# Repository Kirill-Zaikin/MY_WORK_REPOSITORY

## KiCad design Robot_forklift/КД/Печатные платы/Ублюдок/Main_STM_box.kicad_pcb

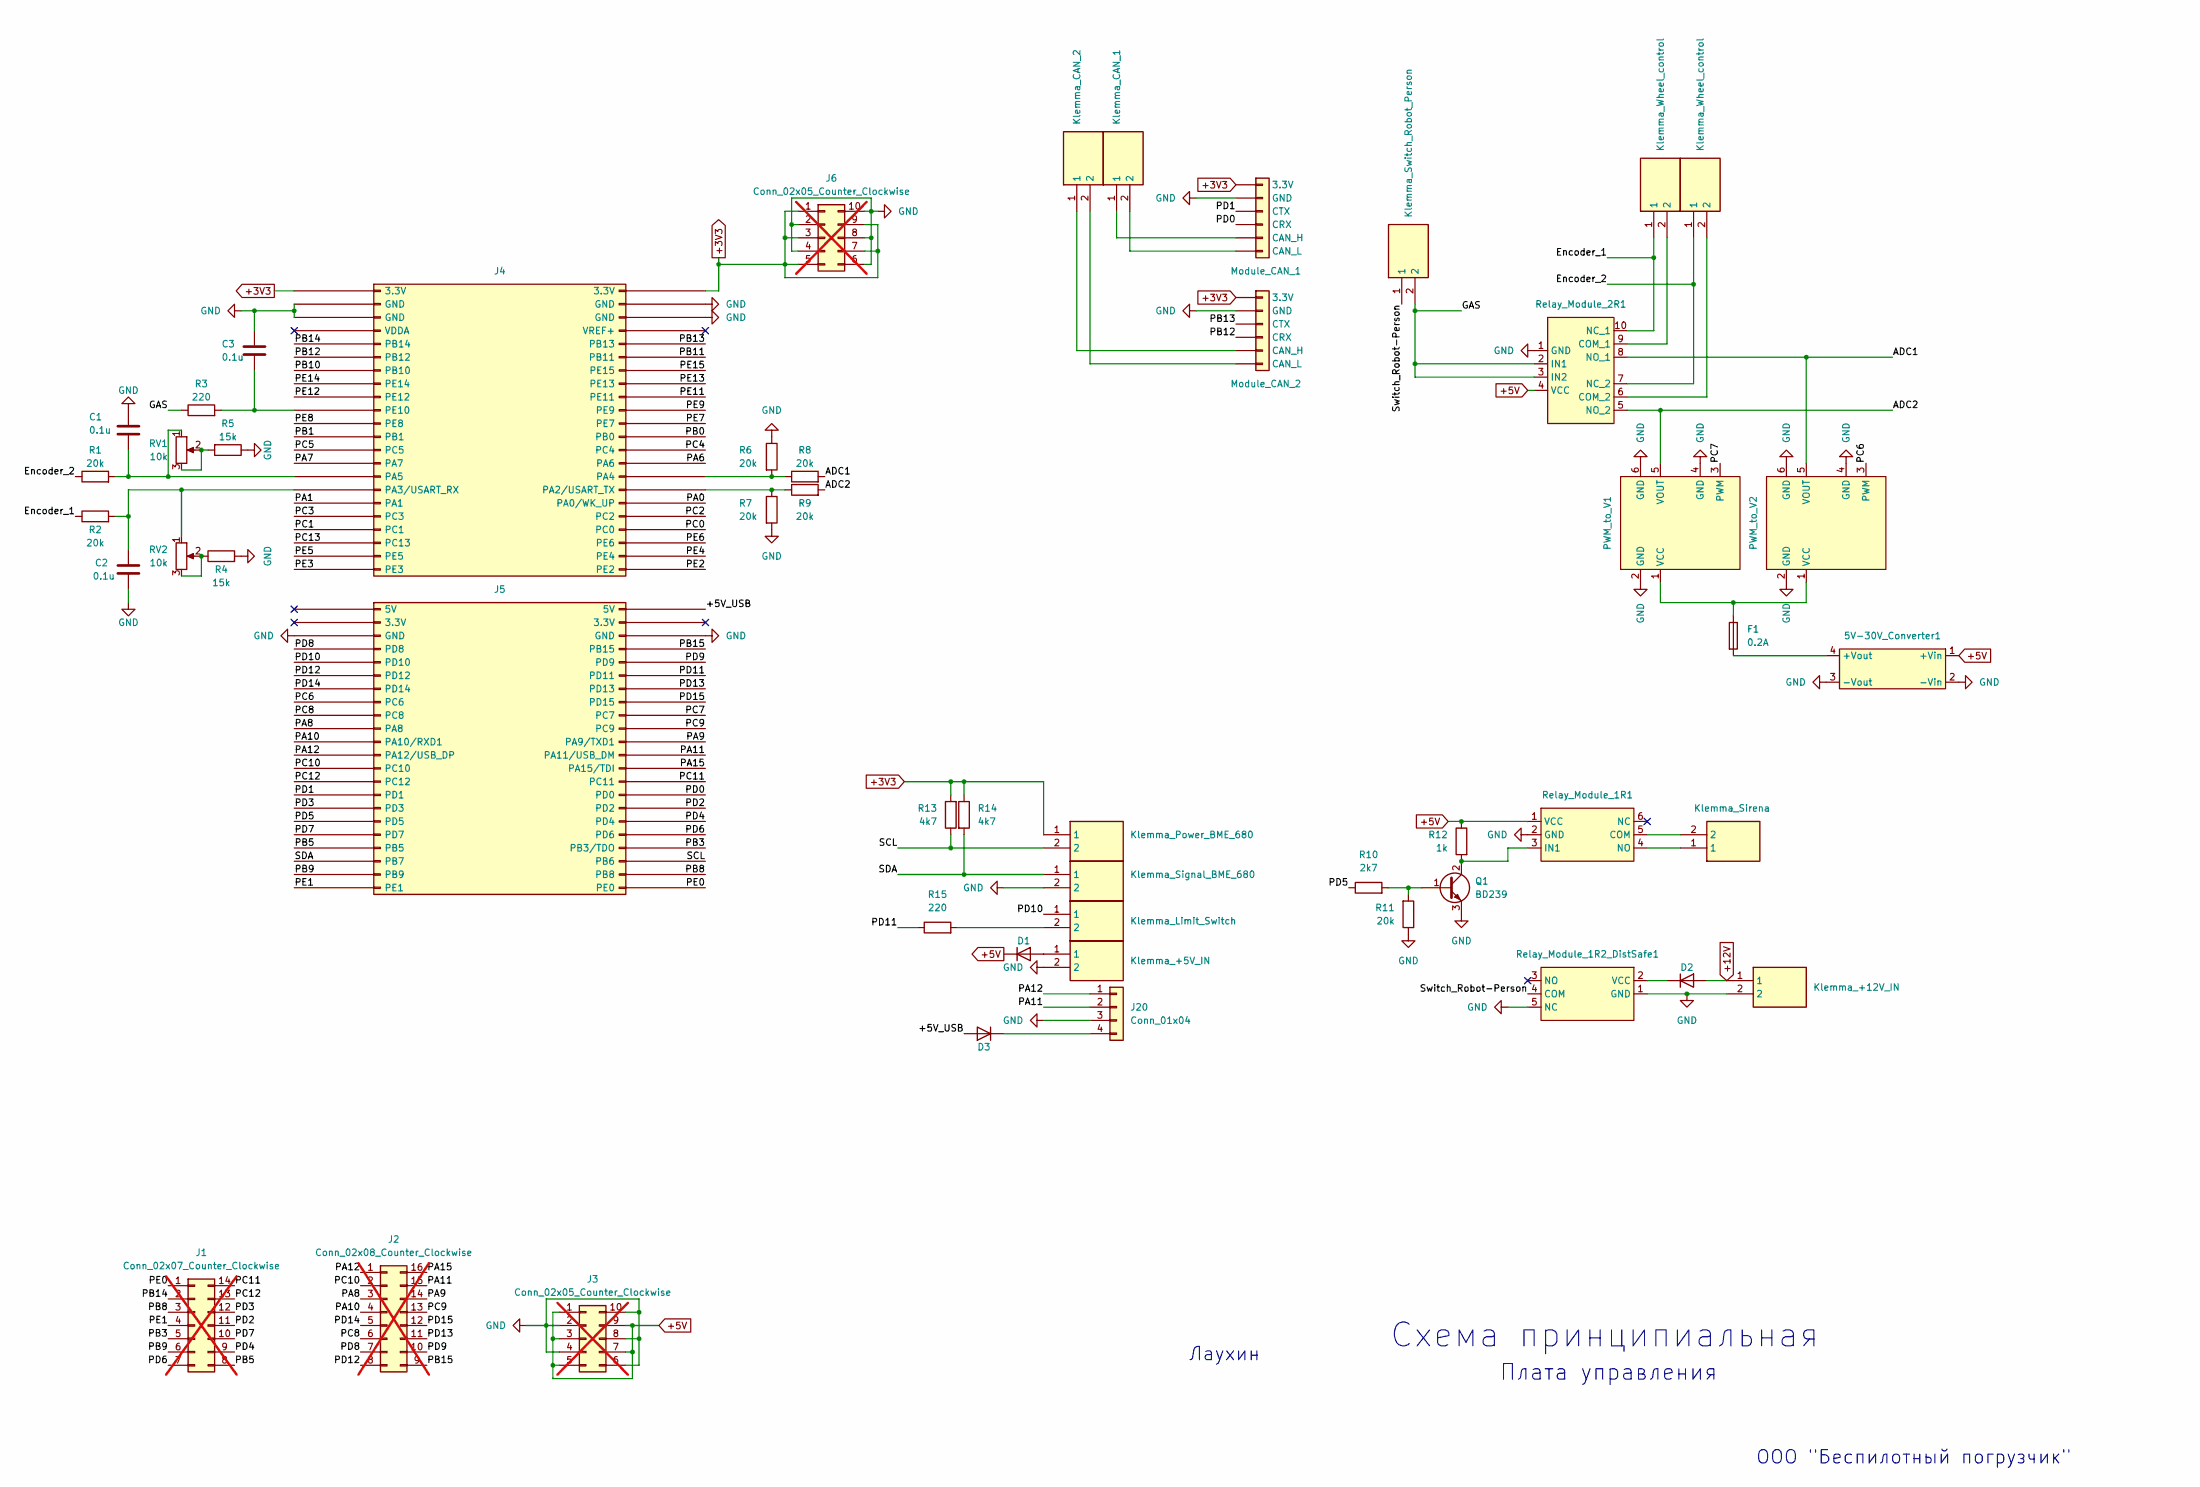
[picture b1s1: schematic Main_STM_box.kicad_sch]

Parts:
5V-30V_Converter1: 5V-30V_Converter; Manufacturer_Part_Number PBS-8 (DS-1023 -1x 8)
C1, C2, C3: 0.1u; C_Axial_L3.8mm_D2.6mm_P10.00mm_Horizontal; Manufacturer_Part_Number К10-17Б 0.1 мкФ X7R,10%, 1206, JYM1H104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
D1, D2, D3: D; D_A-405_P7.62mm_Horizontal; Manufacturer_Part_Number 1N4002
F1: 0.2A; FuseHolder_5x20mm; Manufacturer_Part_Number 2672 пред держ 5x20\закр\2P\\\
J1: Conn_02x07_Counter_Clockwise; PinHeader_2x07_P2.54mm_Vertical; not fitted
J2: Conn_02x08_Counter_Clockwise; PinHeader_2x08_P2.54mm_Vertical; not fitted
J3, J6: Conn_02x05_Counter_Clockwise; PinHeader_2x05_P2.54mm_Vertical; not fitted
J4, J5: Conn_02x22_Odd_Even; PinSocket_2x22_P2.54mm_Vertical; Manufacturer_Part_Number PBD-44 (DS1023-2x22S21)
J7: Klemma_Power_BME_680; KF3012P; Manufacturer_Part_Number KF301-2P
J8: Klemma_Signal_BME_680; KF3012P; Manufacturer_Part_Number KF301-2P
J9: Klemma_Limit_Switch; KF3012P; Manufacturer_Part_Number KF301-2P
J10: Klemma_+5V_IN; KF3012P; Manufacturer_Part_Number KF301-2P
J11: Klemma_CAN_2; KF3012P; Manufacturer_Part_Number KF301-2P
J12: Klemma_CAN_1; KF3012P; Manufacturer_Part_Number KF301-2P
J13: Module_CAN_1; WCMCU-230; Manufacturer_Part_Number PBD-12 (DS-1023 - 2x6)
J14: Module_CAN_2; WCMCU-230; Manufacturer_Part_Number PBD-12 (DS-1023 - 2x6)
J15: Klemma_Switch_Robot_Person; KF3012P; Manufacturer_Part_Number KF301-2P
J16, J18: Klemma_Wheel_control; KF3012P; Manufacturer_Part_Number KF301-2P
J17: Klemma_Sirena; KF3012P; Manufacturer_Part_Number KF301-2P
J19: Klemma_+12V_IN; KF3012P; Manufacturer_Part_Number KF301-2P
J20: Conn_01x04; JST_XH_B4B-XH-A_1x04_P2.50mm_Vertical
PWM_to_V1, PWM_to_V2: PWMtoV; Manufacturer_Part_Number PBS-3 (DS-1023 - 1x3)
Q1: BD239; Q_Transistor_footprint_NPN_PNP; Manufacturer_Part_Number BD239BTU
R1, R2, R6, R7, R8, R9, R11: 20k; R_Axial_DIN0207_L6.3mm_D2.5mm_P7.62mm_Horizontal; Manufacturer_Part_Number MF-25 (С2-23) 0.25 Вт, 20 кОм, 1%
R3: 220; R_Axial_DIN0207_L6.3mm_D2.5mm_P7.62mm_Horizontal; Manufacturer_Part_Number MF-25 (С2-23) 0.25 Вт, 220 Ом, 1%
R4, R5: 15k; R_Axial_DIN0207_L6.3mm_D2.5mm_P7.62mm_Horizontal; Manufacturer_Part_Number MF-25 (С2-23) 0.25 Вт, 15 кОм, 1%
R10: 2k7; R_Axial_DIN0207_L6.3mm_D2.5mm_P7.62mm_Horizontal; Manufacturer_Part_Number MF-25 (С2-23) 0.25 Вт, 2.7 кОм, 1%
R12: 1k; R_Axial_DIN0207_L6.3mm_D2.5mm_P7.62mm_Horizontal; Manufacturer_Part_Number MF-25 (С2-23) 0.25 Вт, 1 кОм, 1%
R13, R14: 4k7; R_Axial_DIN0207_L6.3mm_D2.5mm_P7.62mm_Horizontal; Manufacturer_Part_Number MF-25 (С2-23) 0.25 Вт, 4.7 кОм, 1%
R15: 220; R_Axial_DIN0207_L6.3mm_D2.5mm_P7.62mm_Horizontal
RV1, RV2: 10k; VSE_Potentiometers_W103_3296; Manufacturer_Part_Number 3296W-1-103LF (СП5-2ВБ), 10 кОм
Relay_Module_1R1: Relay_Module_1R; Manufacturer_Part_Number PBS-5 (DS-1023 - 1x5) + PBS-3 (DS-1023 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
Relay_Module_1R2_DistSafe1: Distance_Relay_Module; Manufacturer_Part_Number PBS-3 (DS-1023 - 1x3) + PBS-9 (DS1023-1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
Relay_Module_2R1: Relay_Module_2R; Manufacturer_Part_Number PBS-4 (DS-1023 - 1x4) + PBS-11 (DS1023-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

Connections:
+3V3: J4.1 (3.3V), J4.2 (3.3V), J6.1, J6.3, J6.5, J6.7, J6.9, J7.1, J13.1 (3.3V), J14.1 (3.3V), R13.2, R14.1
+5V: 5V-30V_Converter1.1 (+Vin), D1.1 (K), J3.1, J3.3, J3.5, J3.7, J3.9, R12.1, Relay_Module_1R1.1 (VCC), Relay_Module_2R1.4 (VCC)
+12V: D2.2 (A), J19.1
/+5V_USB: D3.2 (A), J5.2 (5V)
/ADC1: PWM_to_V2.5 (VOUT), R8.2, Relay_Module_2R1.8 (NO_1)
/ADC2: PWM_to_V1.5 (VOUT), R9.2, Relay_Module_2R1.5 (NO_2)
/Encoder_1: J16.1, R2.1, Relay_Module_2R1.10 (NC_1)
/Encoder_2: J18.1, R1.1, Relay_Module_2R1.7 (NC_2)
/GAS: J15.2, R3.1, Relay_Module_2R1.2 (IN1), Relay_Module_2R1.3 (IN2)
/PA0: J4.34 (PA0/WK_UP)
/PA1: J4.33 (PA1)
/PA6: J4.28 (PA6)
/PA7: J4.27 (PA7)
/PA8: J2.3, J5.19 (PA8)
/PA9: J2.14, J5.22 (PA9/TXD1)
/PA10: J2.4, J5.21 (PA10/RXD1)
/PA11: J2.15, J5.24 (PA11/USB_DM), J20.2
/PA12: J2.1, J5.23 (PA12/USB_DP), J20.1
/PA15: J2.16, J5.26 (PA15/TDI)
/PB0: J4.24 (PB0)
/PB1: J4.23 (PB1)
/PB3: J1.5, J5.38 (PB3/TDO)
/PB5: J1.8, J5.37 (PB5)
/PB8: J1.3, J5.42 (PB8)
/PB9: J1.6, J5.41 (PB9)
/PB10: J4.13 (PB10)
/PB11: J4.12 (PB11)
/PB12: J4.11 (PB12), J14.4 (CRX)
/PB13: J4.10 (PB13), J14.3 (CTX)
/PB14: J1.2, J4.9 (PB14)
/PB15: J2.9, J5.8 (PB15)
/PC0: J4.38 (PC0)
/PC1: J4.37 (PC1)
/PC2: J4.36 (PC2)
/PC3: J4.35 (PC3)
/PC4: J4.26 (PC4)
/PC5: J4.25 (PC5)
/PC6: J5.15 (PC6), PWM_to_V2.3 (PWM)
/PC7: J5.18 (PC7), PWM_to_V1.3 (PWM)
/PC8: J2.6, J5.17 (PC8)
/PC9: J2.13, J5.20 (PC9)
/PC10: J2.2, J5.25 (PC10)
/PC11: J1.14, J5.28 (PC11)
/PC12: J1.13, J5.27 (PC12)
/PC13: J4.39 (PC13)
/PD0: J5.30 (PD0), J13.4 (CRX)
/PD1: J5.29 (PD1), J13.3 (CTX)
/PD2: J1.11, J5.32 (PD2)
/PD3: J1.12, J5.31 (PD3)
/PD4: J1.9, J5.34 (PD4)
/PD5: J5.33 (PD5), R10.1
/PD6: J1.7, J5.36 (PD6)
/PD7: J1.10, J5.35 (PD7)
/PD8: J2.7, J5.7 (PD8)
/PD9: J2.10, J5.10 (PD9)
/PD10: J5.9 (PD10), J9.1
/PD11: J5.12 (PD11), R15.1
/PD12: J2.8, J5.11 (PD12)
/PD13: J2.11, J5.14 (PD13)
/PD14: J2.5, J5.13 (PD14)
/PD15: J2.12, J5.16 (PD15)
/PE0: J1.1, J5.44 (PE0)
/PE1: J1.4, J5.43 (PE1)
/PE2: J4.44 (PE2)
/PE3: J4.43 (PE3)
/PE4: J4.42 (PE4)
/PE5: J4.41 (PE5)
/PE6: J4.40 (PE6)
/PE7: J4.22 (PE7)
/PE8: J4.21 (PE8)
/PE9: J4.20 (PE9)
/PE11: J4.18 (PE11)
/PE12: J4.17 (PE12)
/PE13: J4.16 (PE13)
/PE14: J4.15 (PE14)
/PE15: J4.14 (PE15)
/SCL: J5.40 (PB6), J7.2, R13.1
/SDA: J5.39 (PB7), J8.1, R14.2
/Switch_Robot-Person: J15.1, Relay_Module_1R2_DistSafe1.4 (COM)
GND: 5V-30V_Converter1.2 (-Vin), 5V-30V_Converter1.3 (-Vout), C1.1, C2.1, C3.1, J3.2, J3.4, J3.6, J3.8, J3.10, J4.3 (GND), J4.4 (GND), J4.5 (GND), J4.6 (GND), J5.5 (GND), J5.6 (GND), J6.2, J6.4, J6.6, J6.8, J6.10, J8.2, J10.2, J13.2 (GND), J14.2 (GND), J19.2, J20.3, PWM_to_V1.2 (GND), PWM_to_V1.4 (GND), PWM_to_V1.6 (GND), PWM_to_V2.2 (GND), PWM_to_V2.4 (GND), PWM_to_V2.6 (GND), Q1.3 (E), R4.2, R5.1, R6.1, R7.2, R11.1, Relay_Module_1R1.2 (GND), Relay_Module_1R2_DistSafe1.1 (GND), Relay_Module_1R2_DistSafe1.5 (NC), Relay_Module_2R1.1 (GND)
unnamed: 5V-30V_Converter1.4 (+Vout), F1.2
unnamed: D1.2 (A), J10.1
unnamed: D2.1 (K), Relay_Module_1R2_DistSafe1.2 (VCC)
unnamed: D3.1 (K), J20.4
unnamed: J4.32 (PA2/USART_TX), R7.1, R9.1
unnamed: C2.2, J4.31 (PA3/USART_RX), R2.2, RV2.1
unnamed: J4.30 (PA4), R6.2, R8.1
unnamed: C1.2, J4.29 (PA5), R1.2, RV1.1
unnamed: C3.2, J4.19 (PE10), R3.2
unnamed: J9.2, R15.2
unnamed: J12.1, J13.5 (CAN_H)
unnamed: J12.2, J13.6 (CAN_L)
unnamed: J11.1, J14.5 (CAN_H)
unnamed: J11.2, J14.6 (CAN_L)
unnamed: F1.1, PWM_to_V1.1 (VCC), PWM_to_V2.1 (VCC)
unnamed: Q1.1 (B), R10.2, R11.2
unnamed: Q1.2 (C), R12.2, Relay_Module_1R1.3 (IN1)
unnamed: R4.1, RV2.2, RV2.3
unnamed: R5.2, RV1.2, RV1.3
unnamed: J17.2, Relay_Module_1R1.5 (COM)
unnamed: J17.1, Relay_Module_1R1.4 (NO)
unnamed: J16.2, Relay_Module_2R1.9 (COM_1)
unnamed: J18.2, Relay_Module_2R1.6 (COM_2)

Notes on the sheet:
ООО "Беспилотный погрузчик"
Плата управления
Схема принципиальная
Лаухин

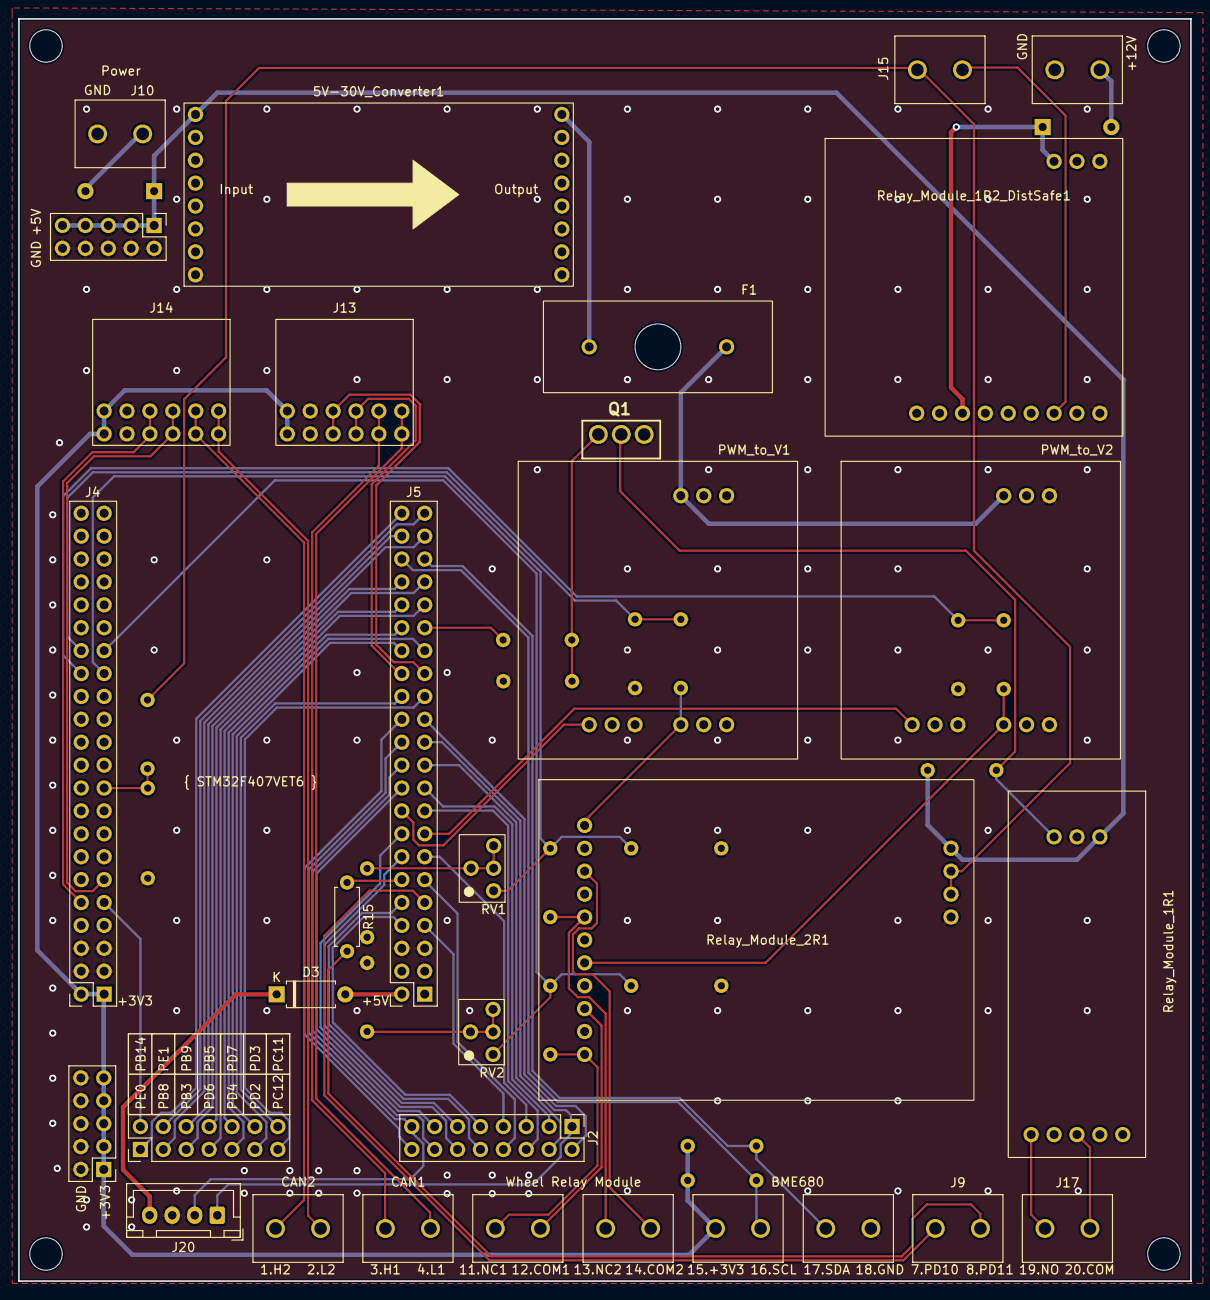
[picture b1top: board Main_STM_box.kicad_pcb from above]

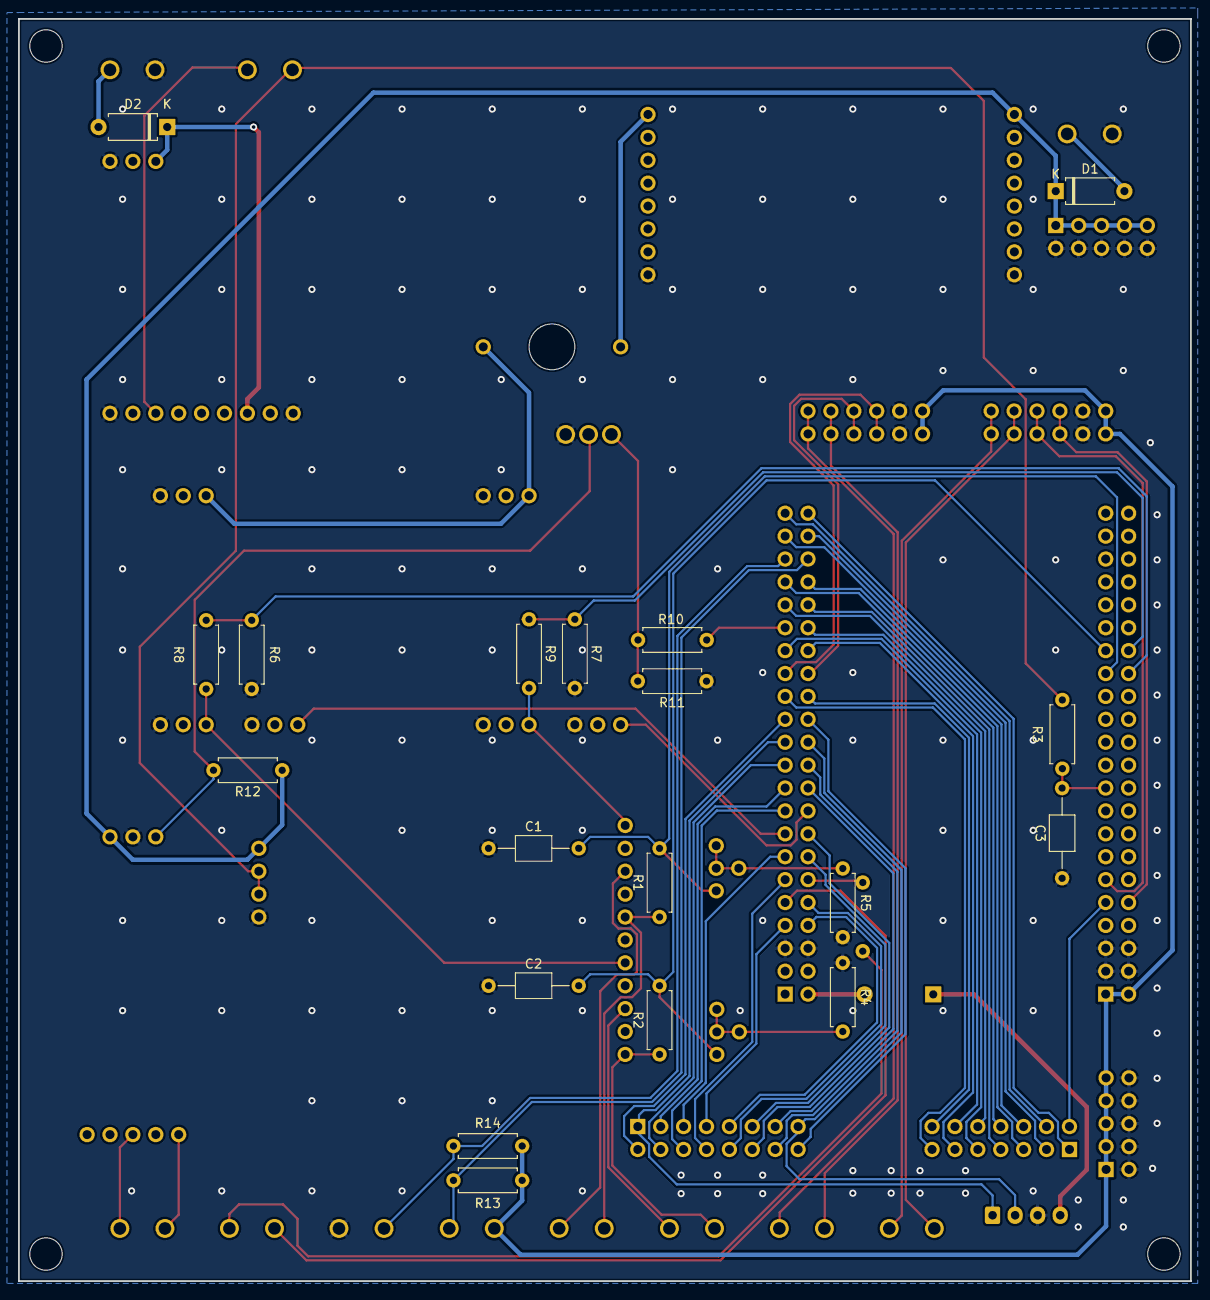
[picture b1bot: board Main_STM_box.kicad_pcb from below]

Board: 2 copper layers, 130.0 x 140.0 mm, 51 parts (21 on the bottom side), 75 nets.

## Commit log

2025-03-12 копим на Лексус
2025-03-29 Наклейки для робота
2025-04-04 Практикум по разводке ПП
2025-04-18 Внесены исправления в схемы Э3
2025-05-22 что-то добавил
2025-06-02 добавлена схема Э4
2025-06-05 Добавлены реквизиты компании
2025-06-13 Добавлены новые госты
2025-06-15 Добавлены ГОСТы по робототехнике
2025-07-11 Добавлены чертежи жгута и ГОСТы
2025-08-18 Слставлен альбом чертежей
2025-08-27 Добавлена папка с наклейками
